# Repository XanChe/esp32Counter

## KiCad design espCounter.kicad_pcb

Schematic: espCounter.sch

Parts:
C1, C2: 10uF; CP_Radial_D5.0mm_P2.50mm
C3, C4: 0.1uF; CP_Radial_D5.0mm_P2.50mm
D1: D; D_A-405_P7.62mm_Horizontal
F1: Fuse; Fuse_Littelfuse-LVR125
J1: Jack-DC; JST_PH_B2B-PH-K_1x02_P2.00mm_Vertical
J2: USB<->ttl; PinHeader_1x03_P2.54mm_Horizontal
J3: SPI_CONN; PinHeader_1x04_P2.54mm_Horizontal
J4: GPIO_5_4_0; PinHeader_1x03_P2.54mm_Horizontal
R1: 470; R_0805_2012Metric_Pad1.15x1.40mm_HandSolder
R4: 10k; R_Axial_DIN0207_L6.3mm_D2.5mm_P15.24mm_Horizontal
R5, R6, R7, R8: 10k; R_0805_2012Metric_Pad1.15x1.40mm_HandSolder
SW1, SW2: SW_Push; SW_PUSH_6mm_H4.3mm
U1: AMS1117-3.3; SOT-223-3_TabPin2
U2: ESP-07

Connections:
/GIPO0: J4.1, R7.2, SW2.1, U2.12
/GPIO2: R8.2, U2.11
/GPIO4: J4.2, U2.13
/GPIO5: J4.3, U2.14
/HSPICS: R6.1, U2.10
/HSPI_CLK: J3.1, U2.5
/HSPI_MISO: J3.2, U2.6
/HSPI_MOSI: J3.3, U2.7
/RXtoTX: J2.2, U2.15
/TXtoRX: J2.3, U2.16
/deepsleep: R1.2, U2.4
unnamed: C1.1, C3.1, D1.1, J1.1, U1.3 (VI)
unnamed: C1.2, C2.2, C3.2, C4.2, F1.2, J1.2, SW1.1, U1.1 (GND)
unnamed: C2.1, C4.1, D1.2, R4.1, R5.1, R7.1, R8.1, U1.2 (VO), U2.8
unnamed: F1.1, R6.2, U2.9
unnamed: J2.1, SW2.2
unnamed: R1.1, R5.2, SW1.2, U2.1
unnamed: R4.2, U2.3

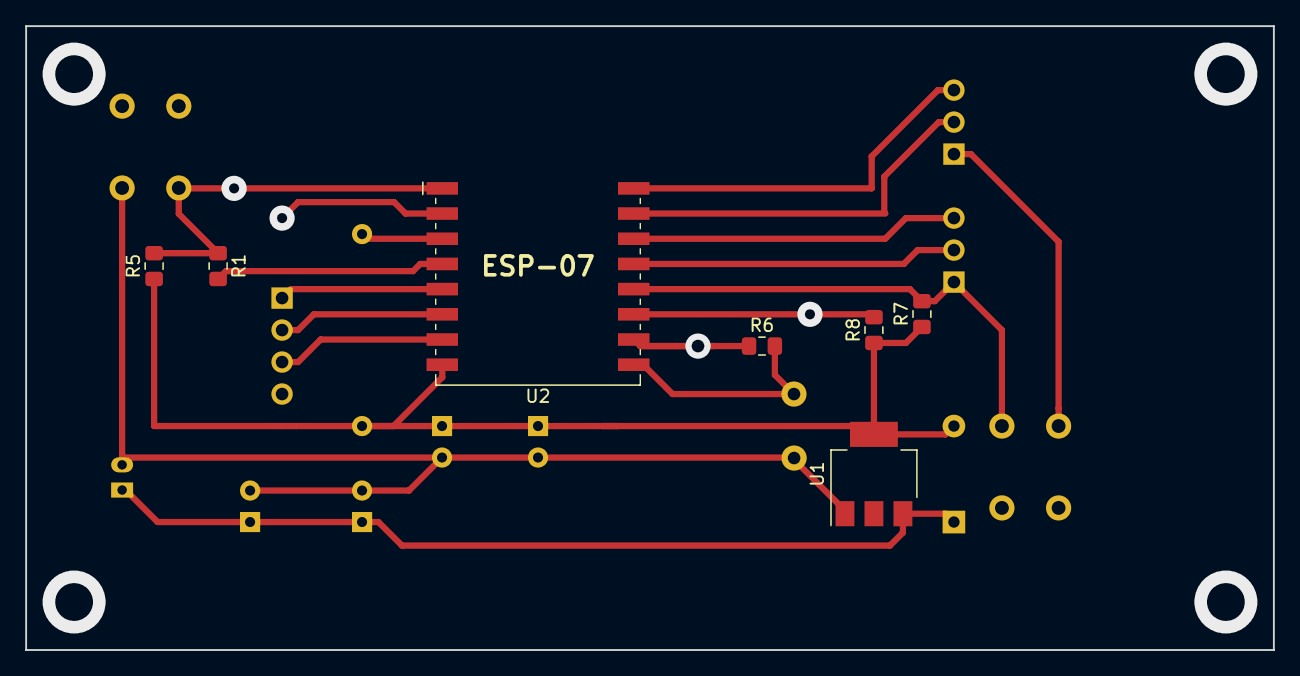
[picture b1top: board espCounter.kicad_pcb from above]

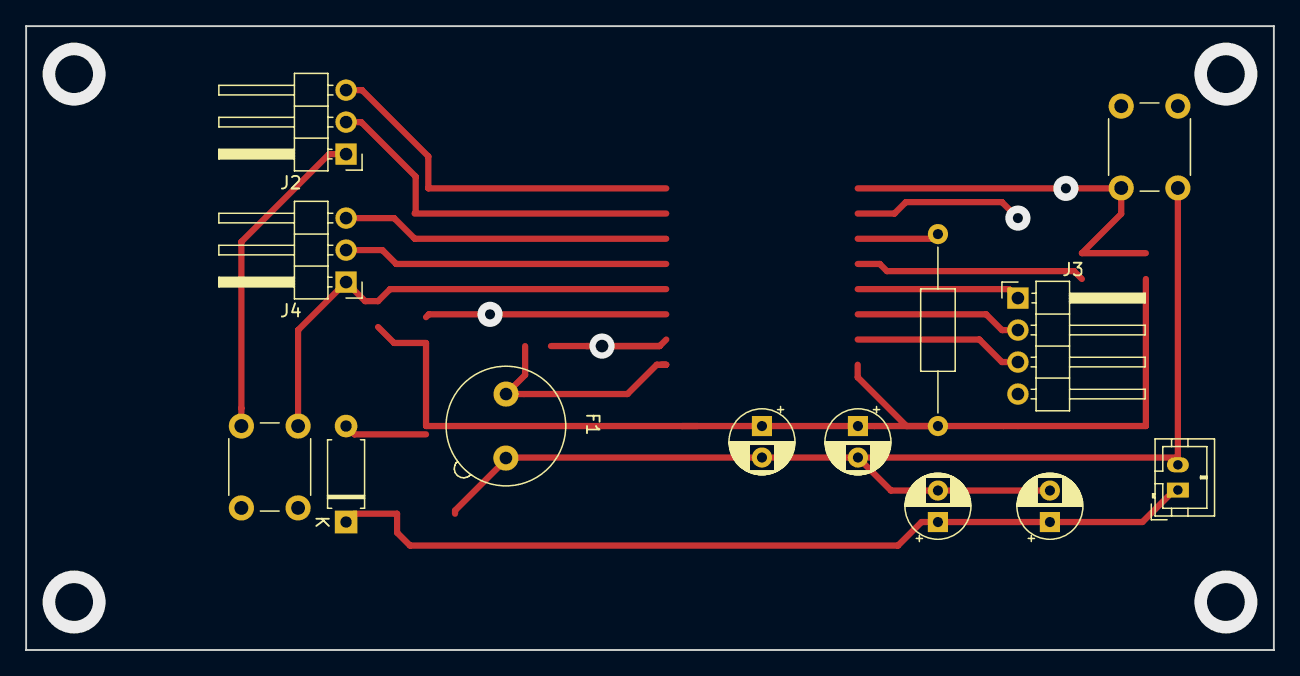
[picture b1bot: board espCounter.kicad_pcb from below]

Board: 2 copper layers, 99.1 x 49.5 mm, 20 parts (13 on the bottom side), 18 nets.

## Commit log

2018-09-14 init project
2018-09-14 neting
2018-09-14 new neting & footdtate
2018-09-14 first trecer
2018-09-14 v1.0 with tatal camoacitor
2018-09-14 v1.01
2018-09-14 rename project
